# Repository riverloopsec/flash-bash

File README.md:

# Flash-BASH
Flash-BASH is a Raspberry Pi based tool that uses a multiplexer to "glitch" a target device into a privileged open state.

## Usage

See our blog post at https://www.riverloopsecurity.com/blog/2021/09/introducing-flash-bash/ for information on usage.

## Install/Compile
The easiest way to use this tool without any tweaks is with a Raspberry Pi Model 3 B+.
However, with minor tweaks to the code, any Raspberry Pi, Arduino, or micro-controller should work fine.

Secondly, this tool is based on the dependency Wiring Pi which you can install like so:
```
sudo apt-get install wiringpi
```

Third, you will need the Pi Hat and components that are included in the CAD folder in this repository. You could also wire this with jumpers and a breadboard or a prototype-hat, but it will not be as organized!

Last, you will need to compile this pointing to the Wiring Pi library like this
```
gcc -o flash_bash flash_bash.c -lwiringPi
```

That should get you started all you have to do now is run the program!
```
sudo ./flash_bash
```

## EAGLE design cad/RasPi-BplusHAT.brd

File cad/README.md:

# Flash-BASH Pi HAT Files
Included are Eagle 9.6.1 CAD files so that you can make modifications. Also included are ready-to-fab gerber files in the CAMOutputs.zip file.

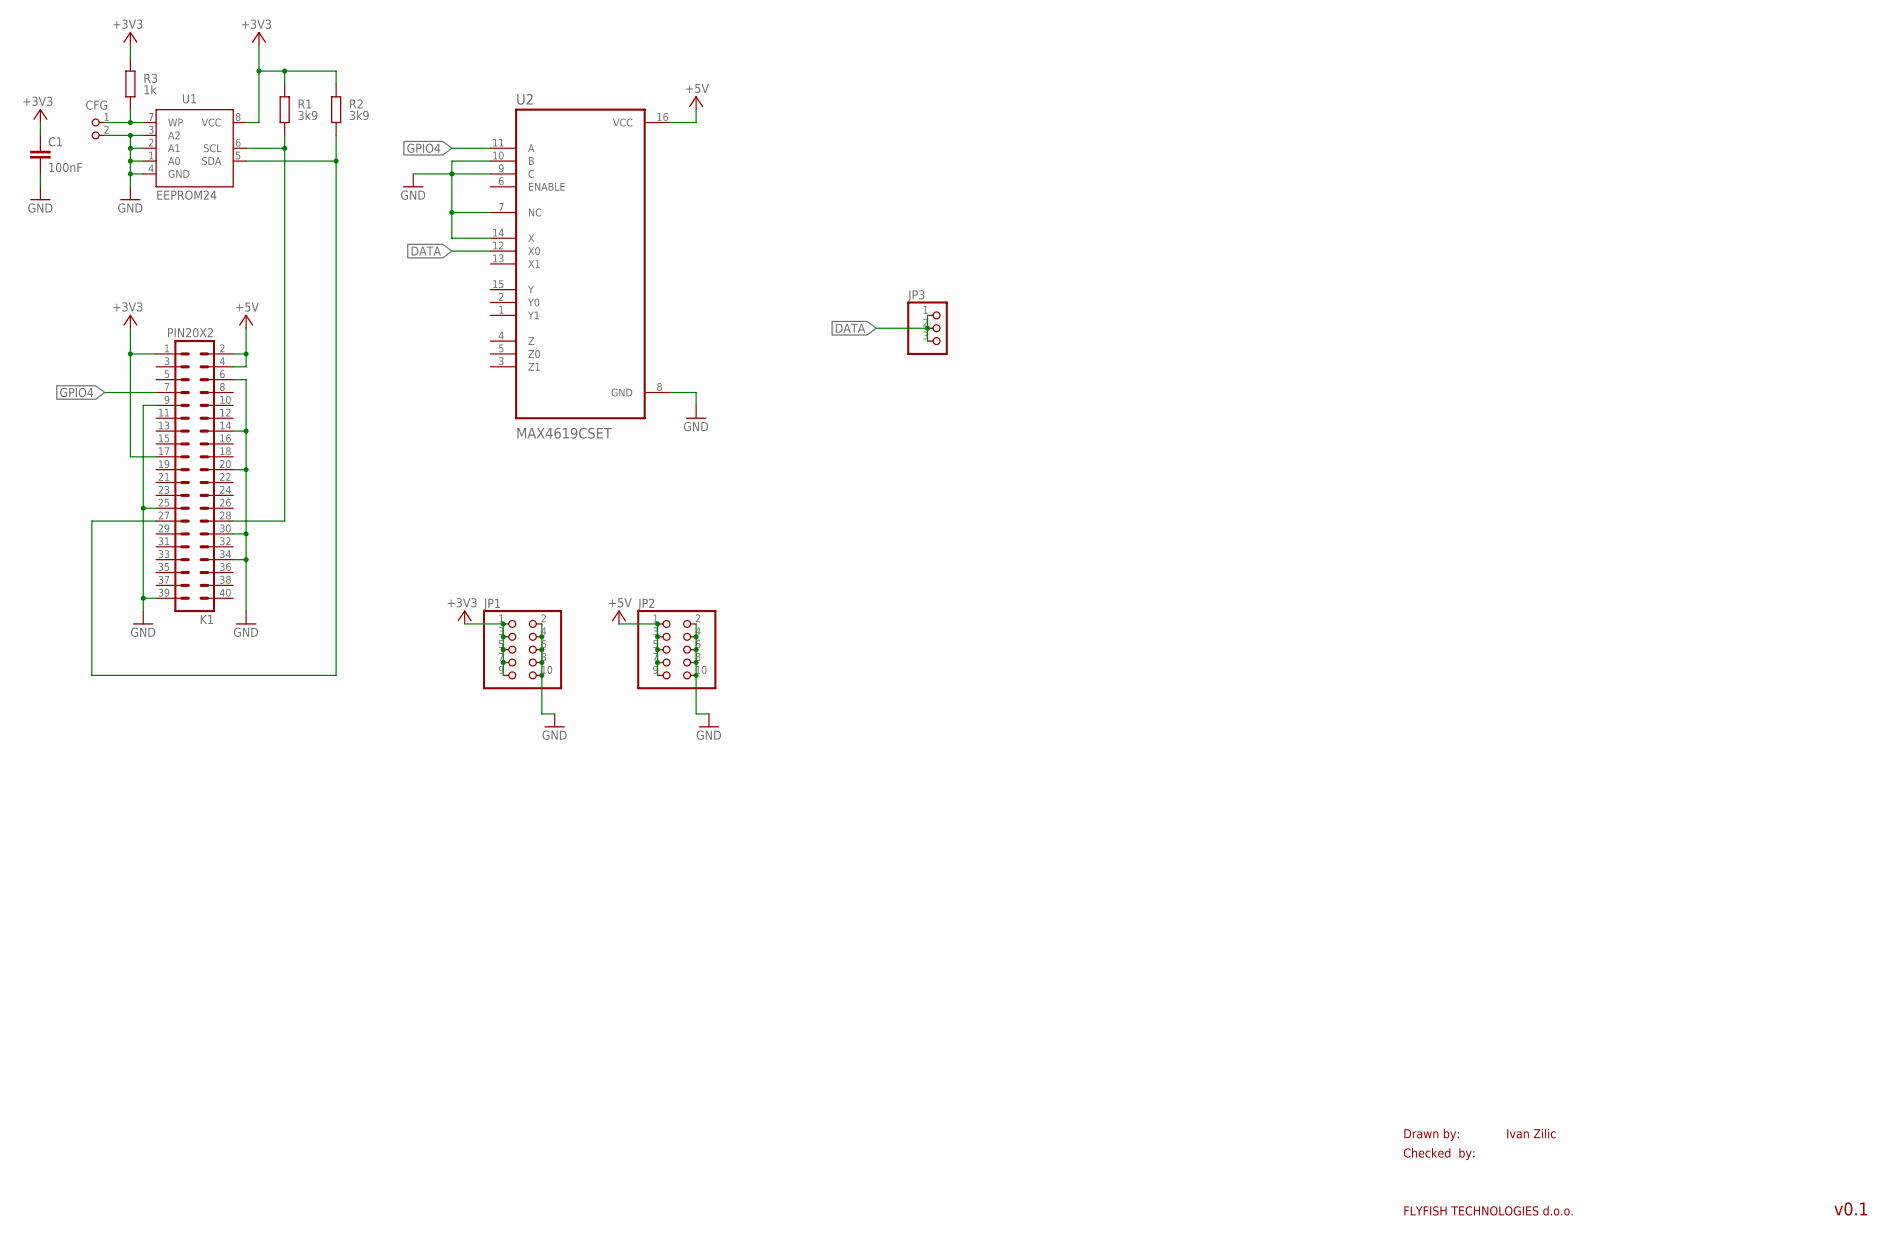
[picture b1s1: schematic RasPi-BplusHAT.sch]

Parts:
C1: 100nF; C0805K
CFG: PIN2_100; PIN_W_2
JP1, JP2: PINHD-2X5; 2X05
JP3: PINHD-1X3; 1X03
K1: PIN20X2; PIN_20X2
R1, R2: 3k9; M0805; TOLERANCE 5%
R3: 1k; M0805; TOLERANCE 5%
U1: EEPROM24; SOIC8
U2: MAX4619CSET; SOIC127P600X175-16N

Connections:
+3V3: C1.1, JP1.1, JP1.3, JP1.5, JP1.7, JP1.9, K1.1, K1.17, R1.2, R2.2, R3.2, U1.8 (VCC)
+5V: JP2.1, JP2.3, JP2.5, JP2.7, JP2.9, K1.2, K1.4, U2.16 (VCC)
DATA: JP3.1, JP3.2, JP3.3, U2.12 (X0)
GND: C1.2, CFG.2, JP1.2, JP1.4, JP1.6, JP1.8, JP1.10, JP2.2, JP2.4, JP2.6, JP2.8, JP2.10, K1.6, K1.9, K1.14, K1.20, K1.25, K1.30, K1.34, K1.39, U1.1 (A0), U1.2 (A1), U1.3 (A2), U1.4 (GND), U2.7 (NC), U2.8 (GND), U2.9 (C), U2.10 (B), U2.14 (X)
GPIO4: K1.7, U2.11 (A)
unnamed: K1.28, R1.1, U1.6 (SCL)
unnamed: K1.27, R2.1, U1.5 (SDA)
unnamed: CFG.1, R3.1, U1.7 (WP)

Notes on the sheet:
Drawn by:
Checked by:
FLYFISH TECHNOLOGIES d.o.o.
Ivan Zilic
v0.1

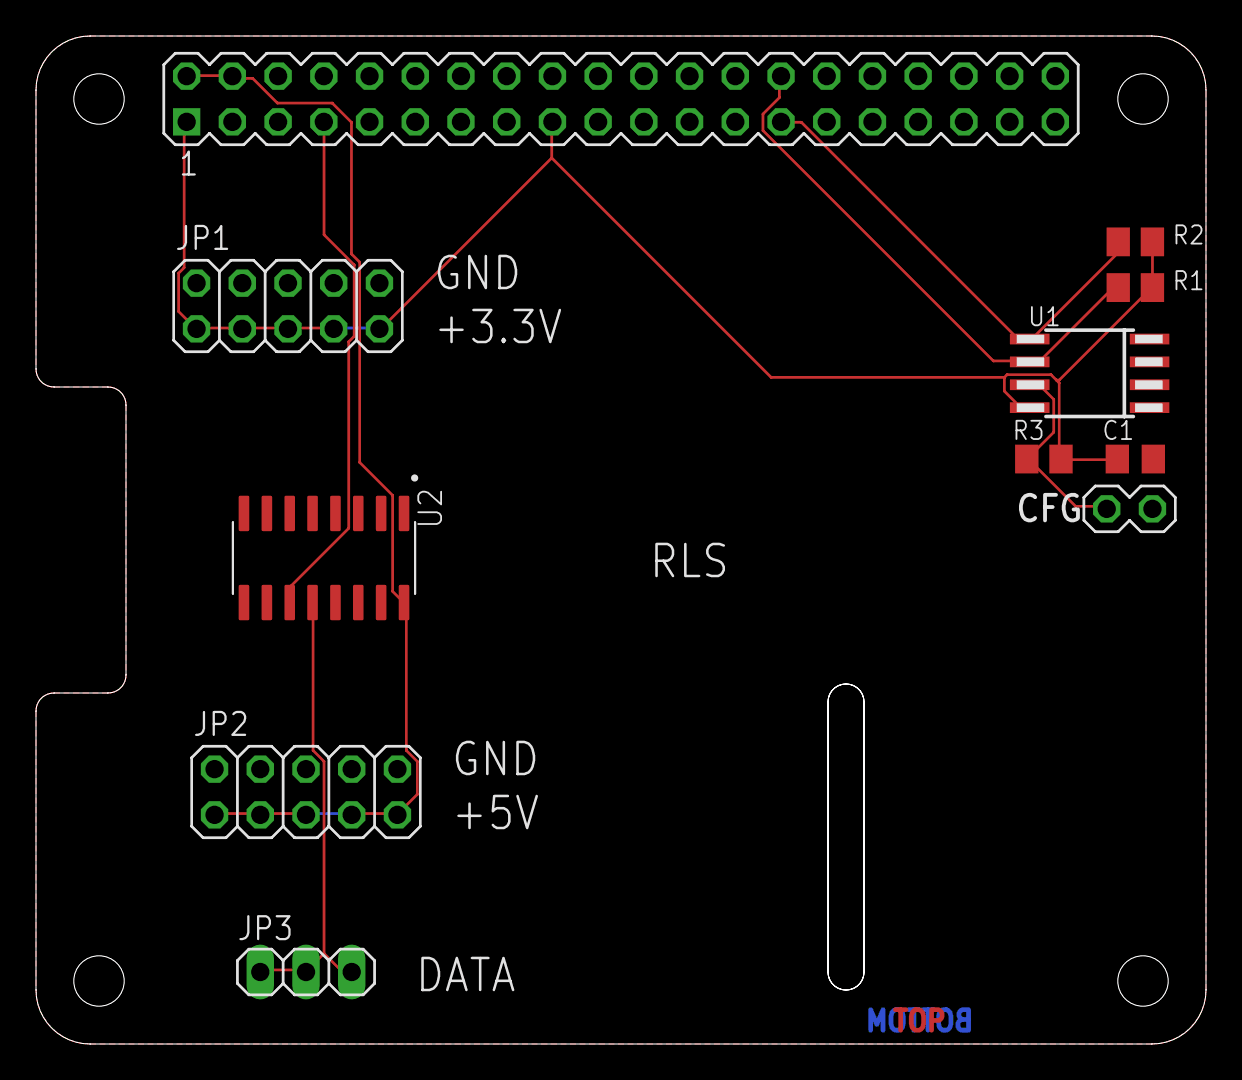
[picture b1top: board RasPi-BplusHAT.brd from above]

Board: 2 copper layers, 65.0 x 56.0 mm, 11 parts (0 on the bottom side), 8 nets.

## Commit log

2021-09-02 Clean commit.
